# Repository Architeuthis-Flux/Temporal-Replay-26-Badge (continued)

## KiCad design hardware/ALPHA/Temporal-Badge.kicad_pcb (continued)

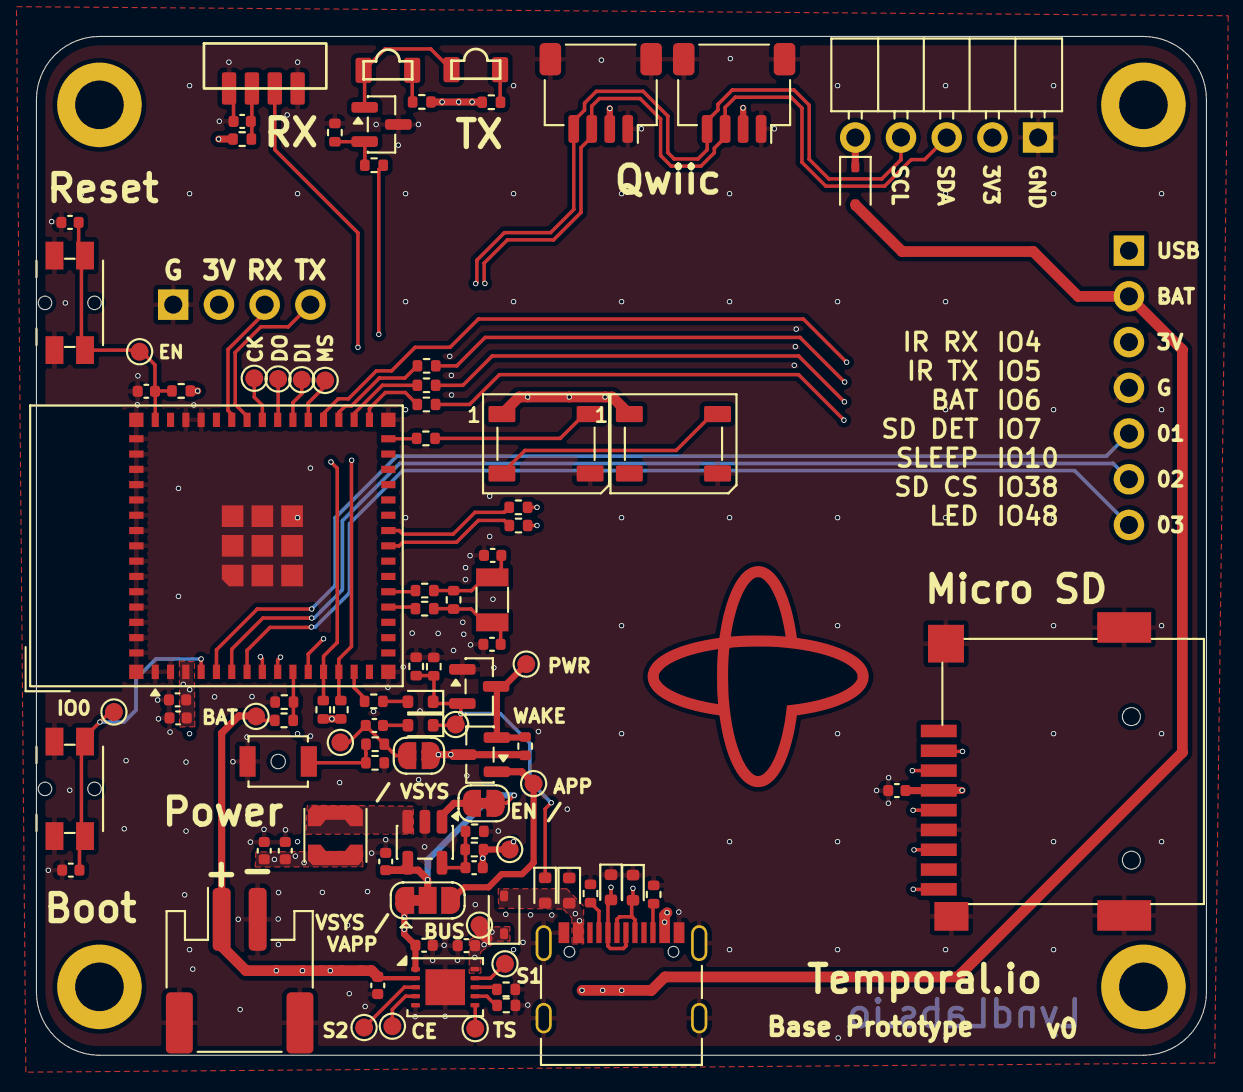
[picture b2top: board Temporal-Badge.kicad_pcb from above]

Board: 4 copper layers, 65.0 x 56.6 mm, 100 parts (0 on the bottom side), 67 nets.

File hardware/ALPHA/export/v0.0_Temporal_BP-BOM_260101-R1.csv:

Designator,Comment,Footprint,LCSC
"C1,C33,C40,C41",22uF,Capacitor_SMD:C_0402_1005Metric,C3845593
"C2,C3,C4,C6,C7",0.1uF,Capacitor_SMD:C_0402_1005Metric,C1525
"C5,C8,C24,C43",1uF,Capacitor_SMD:C_0402_1005Metric,C14445
C25,10uF,Capacitor_SMD:C_0402_1005Metric,C315248
C34,470 nF,Capacitor_SMD:C_0402_1005Metric,C92361
C37,100nF,Capacitor_SMD:C_0402_1005Metric,C1525
C38,22pF,Capacitor_SMD:C_0402_1005Metric,C76960
"D1,D2",D_Schottky,Diode_SMD:D_SOD-323,C60580
"D3,D4,D5",D_TVS,Diode_SMD:D_SOD-523,C3008120
"D6,D7",WS2812B,LED_SMD:LED_WS2812B_PLCC4_5.0x5.0mm_P3.2mm,C114586
"D8,D9,D10",D_Schottky,Diode_SMD:D_SOD-523,C917006
"D14,D15",VSMY14940,Temporal:vsmy14940,C511069
J1,USB C 2.0,Connector_USB:USB_C_Receptacle_Palconn_UTC16-G,C2765186
"J2,J4",Qwiic,Connector_JST:JST_SH_SM04B-SRSS-TB_1x04-1MP_P1.00mm_Horizontal,C51940130
J3,JST PH,Connector_JST:JST_PH_S2B-PH-SM4-TB_1x02-1MP_P2.00mm_Horizontal,C295747
J8,Micro-SD,Temporal:MicroSD,C381082
L5,2.2uF,Inductor_SMD:L_Coilcraft_LPS3010,C2926400
Q1,DMN2058UW / 2N3904,Package_TO_SOT_SMD:SOT-23,C54879
Q3,AO3401A,Package_TO_SOT_SMD:SOT-23,C15127
Q4,L2N7002SDW,Package_TO_SOT_SMD:SOT-23,C383163
"R1,R2,R3,R4,R5,R11,R12,R13,R17",0,Resistor_SMD:R_0402_1005Metric,C106231
"R6,R38",10K,Resistor_SMD:R_0402_1005Metric,C60490
"R7,R8",4.7K,Resistor_SMD:R_0402_1005Metric,C105871
"R9,R10,R18",5.1K,Resistor_SMD:R_0402_1005Metric,C25905
R14,680K,Resistor_SMD:R_0402_1005Metric,C163456
R15,150K,Resistor_SMD:R_0402_1005Metric,C93947
R16,1K,Resistor_SMD:R_0402_1005Metric,C106235
"R19,R22,R34",100K,Resistor_SMD:R_0402_1005Metric,C60491
"R20,R23",220K,Resistor_SMD:R_0402_1005Metric,C25767
"R30,R31",470K,Resistor_SMD:R_0402_1005Metric,C137976
"R36,R37",39,Resistor_SMD:R_0402_1005Metric,C185420
R39,150,Resistor_SMD:R_0402_1005Metric,C138054
R40,10,Resistor_SMD:R_0402_1005Metric,C138066
SW1,Reset,Button_Switch_SMD:Panasonic_EVQPUL_EVQPUC,C79174
SW2,BOOT,Button_Switch_SMD:Panasonic_EVQPUL_EVQPUC,C79174
SW3,Latch,Button_Switch_SMD:SW_SPST_B3U-1000P-B,C49234121
U1,ESP32-S3-MINI-1,RF_Module:ESP32-S2-MINI-1,C3013906
U5,BQ25185,Package_SON:WSON-10-1EP_4x3mm_P0.5mm_EP2.2x2mm,C19725033
U10,SY8089,Package_TO_SOT_SMD:SOT-23-5,C79313
Y1,32.768KHz,Crystal:Crystal_SMD_3215-2Pin_3.2x1.5mm,C97606

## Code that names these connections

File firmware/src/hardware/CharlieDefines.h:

#ifndef CHARLIE_DEFINES_H
#define CHARLIE_DEFINES_H

#define JOY_Y 1
#define JOY_X 2

#define BUTTON_RIGHT 4
#define BUTTON_DOWN  5
#define BUTTON_LEFT  6 //this is marked as X on schematic. You need to move the 0 ohm resistor to the other position.
#define BUTTON_UP    7

#define SDA_PIN 8
#define SCL_PIN 9

#define IR_RX_PIN 10 //TSOP75338 
#define IR_TX_PIN 11

#define MCU_SLEEP_PIN 12
#define INT_PWR_PIN 13
#define INT_GP_PIN 14  // For the LIS2DH12TR accelerometer (interrupt / SA0 per schematic) Also SYSOFF for BQ24079

#define NAPTIME_LIGHT_SLEEP_AFTER_NO_MOTION_MS 30000UL
#define NAPTIME_DEEP_SLEEP_AFTER_NO_MOTION_MS 300000UL
#define NAPTIME_LIGHT_SLEEP_POLL_MS 1000UL

#define MOTOR_PIN 21

#define LIS2DH12_I2C_ADDRESS 0x19

#define LED_MATRIX_INTB_PIN 17    //IS31FL3731 LED Matrix driver
#define LED_MATRIX_AUDIO_PIN 18
#define LED_MATRIX_ENABLE_PIN 47

#define LED_MATRIX_WIDTH 8
#define LED_MATRIX_HEIGHT 8
#define LED_MATRIX_I2C_ADDRESS 0x74

#define LCD_RES_PIN 38 // disconnected with solder jumper

#define OLED_I2C_ADDRESS 0x3C

#define OLED_WIDTH 128
#define OLED_HEIGHT 64

//This is for Kevin's board, comment this out if your name is not Kevin
// #define BATT_VOLTAGE_PIN 3 // VBATT - 150K - BATT_VOLTAGE_PIN - 150K - GND //I just bodged this in on my board for testing
// #define BADGE_ECHO

// ── Per-peripheral feature flags ─────────────────────────────────────────────
// Code includes/excludes hardware drivers based on these flags.
// Add matching flags to any new hardware config file to enable the peripheral.
#define BADGE_HAS_IMU           // LIS2DH12 accelerometer
#define BADGE_HAS_LED_MATRIX    // IS31FL3731 8×8 LED matrix
#define BADGE_HAS_HAPTICS       // Vibration motor
#define BADGE_HAS_BATTERY_GAUGE // MAX17048 fuel gauge
#define BADGE_HAS_SLEEP_SERVICE // Motion-based sleep (requires IMU)


#define BADGE_CHARLIE


#endif

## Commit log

2026-05-07 Boot splash + battery alternation + shutdown hold + factory flash tooling
    - BootSplash: temporal-logo starfield played in setup() with hardware
    contrast fade-in/out and per-star scintillation; LED matrix mirrors
    with bounded sparkles. Bottom-right corner shows FIRMWARE_VERSION.
    - BadgeVersion.h: tagged baseline v0.0.0 for shipping.
    - OLEDLayout: battery glyph alternates with the two-digit percent on a
    shared ~1.6s cadence so charging / full / critical states still show
2026-05-07 v0.1.1 make micropython more vanilla,
2026-05-07 fix booping
2026-05-07 bump badge version
2026-05-07 make the version number print from a single source
2026-05-07 factory build
2026-05-07 mass flasher and tardigotchi
2026-05-07 Adding more updates
2026-05-07 factory bin
2026-05-07 rts and dtr updates
2026-05-08 artificial horizon clock thing, return background LED matrix apps, add tardagotchi to the led matrix when exited
2026-05-08 power: batch probe ADC reads via Policy::probeSamplesPerTick (default 3)
    Cuts BQ24079 CE-high time per probe from ~scheduler-cadence × samples to
    ~probe-burst duration, reclaiming charging duty cycle lost to inter-tick yields.
2026-05-08 power: convert to esp_logi format.
    should make it easy to silence messages depending on the log level now
2026-05-09 make draw app better (automatic fields from badge info, help text, nametag prompts, in place text resizing and font), add artificial hoizon clock, allow reordering home screen icons, add more setting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
2026-05-09 buncha fixes, added help, QR codes to all the links, auto recover startup files, comment out other build envs, new icons,
2026-05-09 add wifi support for multiple networks to check, OTA firmware updates, opt in repartitioning (to claim that unused 2MB), fix config loading, idk like a billion little ui fixes
2026-05-10 file viewer / editor, gh actions to put doom in releases, online registry to download doom, fixin' stuff
2026-05-10 IDF: Add native ESP-IDF build path
    This does not change the pioarduino flow, and registers firmware/src/ as the IDF main component with vendored Arduino libs (U8g2, ArduinoJson, Adafruit_*, SparkFun_LIS2DH12) and a layered sdkconfig.d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
    Introduces an echo-dev-idf PlatformIO env so idf.py build, pio run -e echo-dev, and pio run -e echo-dev-idf all produce the same 16MB-doom firmware image.
2026-05-10 Changes before error encountered
    Agent-Logs-Url: https://github.com/Architeuthis-Flux/Temporal-Replay-26-Badge/sessions/ccf519e2-c049-484c-a4d6-95e28268dd7b
2026-05-10 git: remove annoying vscode folder
    this is user facing, and should never be committed to the repository
2026-05-10 GUI: Move games to game sub-menu
    The submenu reuses GridMenuScreen so back-button (cancel) and footer glyphs work for free, and games are no longer hidden behind BADGE_DEV_MENU.
2026-05-10 fix some keyboard weirdness, fix doomload failures
2026-05-10 unbake filesystem in firmware, add community registry, add credits, shuffle home screen
2026-05-11 put doom in the makifest
2026-05-11 untested ir app
2026-05-11 ir_remote: add curated code modules, clean pyc
    Remove checked-in Python bytecode and stale ir_remote scripts, add curated IR code data and reorganize the IR playground. Updates include:
    - .gitignore: ignore __pycache__/, *.pyc, *.pyo
    - Delete many ir_remote .py and __pycache__ files that shouldn't be committed
    - Add new curated data modules: ac_codes.py, audio_codes.py, projector_codes.py, tv_codes.py
    - Add new/updated ir_remote apps (remote, scan, range, games) and modify ir_lib/main to match
    - Update manifest, startup/generator scripts and docs: README now documents the dev force-refresh workflow (build-time flag and runtime marker)
2026-05-11 fix battery percentage because it was blocking the wifi from connecting on battery, unmove tardagotchi (I accidentally dragged the folder into breaksnake)
2026-05-12 fix battery bullshit with the algorithm not getting a reading and blocking wifi
2026-05-14 Bump firmware version to 0.2.5
2026-05-14 okay I screwed up tags, we're bumping to 0.2.6
2026-05-15 Flesh out micropython, disable led matrix flipping, add a new path for community apps, fix some ota nonsense, add readmes for micropython imports and community apps
2026-05-15 chore(registry): regenerate community_apps.json [skip ci]
2026-05-15 allow force updating firmware OTA
2026-05-15 very rainbowy flash gui, gated debugs, decrashified
2026-05-15 fix ota connection refusal by relieving heap pressure, set fixed led matrix orientation to upright
2026-05-16 fix(ota): preserve TLS memory for updates
2026-05-16 fix(ota): stream GitHub release assets reliably
2026-05-16 feat(ota): refine firmware update progress UI
2026-05-16 fix more heap ota stuff
2026-05-16 fix(ota): address review feedback
2026-05-16 fix(ota-ui): style danger modals
2026-05-16 chore(ota): remove TLS client patch
2026-05-16 Bump firmware version to 0.2.9
2026-05-16 fix ota for different partition tables
2026-05-16 we're just gonna bump versions on every commit, I'm sick of messing up tags
2026-05-16 make ota less flaky and allow for reparitioning to the bigger table (_ver2.csv)
2026-05-16 chore: bump firmware to v0.2.10 [skip ci]
2026-05-17 make a screenshot call for python to print the OLED and led matrix to the terminal, (it's either screenshot(size = 0) or just 'o'
2026-05-17 chore: bump firmware to v0.2.11 [skip ci]
2026-05-17 fix screenshot scaling to better match the physical layout, put all hardcoded links into a single file (for easy migration over to Temporal hosted repo), keep leading v in the version numbers for dis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
2026-05-17 added docs for screenshots, allow hiding apps not on the filesystem
2026-05-17 chore: bump firmware to v0.2.12 [skip ci]
2026-05-17 fix action packed race
2026-05-17 chore: bump firmware to v0.2.13 [skip ci]
2026-05-17 cleared up so much internal ram, fixed drawing nametag mode, add heap diagnostics
2026-05-17 chore: bump firmware to v0.2.14 [skip ci]
2026-05-17 very minor fix where exiting a menu put the cursor in th wrong place
2026-05-17 chore: bump firmware to v0.2.15 [skip ci]
2026-06-02 add sockets, espnow, and ssl to the micropython build
2026-06-02 chore: bump firmware to v0.2.16 [skip ci]
2026-06-04 fix WLAN module
2026-06-04 chore: bump firmware to v0.2.17 [skip ci]
